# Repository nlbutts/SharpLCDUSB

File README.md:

# SharpLCDUSB
Small USB device for the Sharp Memory LCD

# Requirements

This was developed using Kicad 5.1.8.

Digikey Github library hash:
https://github.com/digikey/digikey-kicad-library
e10fdb74d46ad9f1668ed96b06f4c25e4f1bcf4c

My personal Kicad libraries:
https://github.com/nlbutts/KicadLib
dcbc8002b31520b4c2474bcd5f2975a0abc3e0ea

https://github.com/nlbutts/KicadFootprint
a663d1c8cb2ec06ade98de852019e83a467398e3

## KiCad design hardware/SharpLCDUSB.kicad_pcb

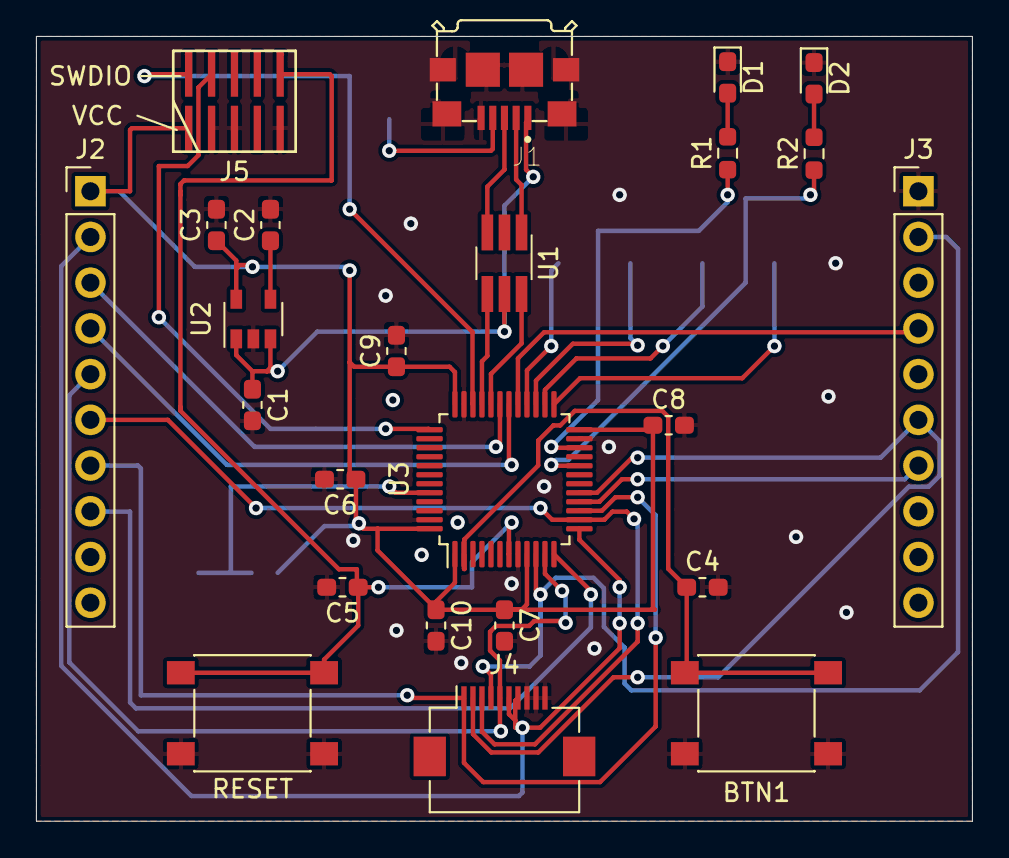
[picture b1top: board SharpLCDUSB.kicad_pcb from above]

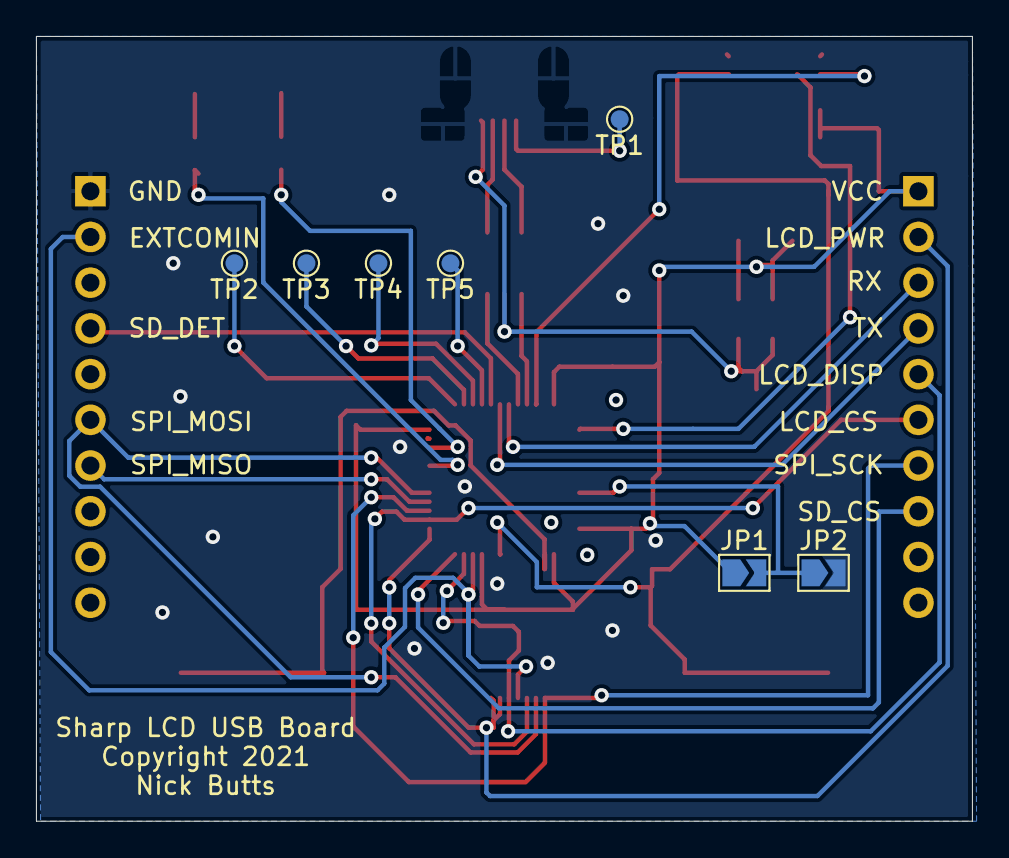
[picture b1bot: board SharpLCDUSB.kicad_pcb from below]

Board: 2 copper layers, 52.0 x 43.6 mm, 31 parts (7 on the bottom side), 33 nets.

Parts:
C1, C3: 10u; C_0603_1608Metric_Pad1.05x0.95mm_HandSolder
C2: 0.01u; C_0603_1608Metric_Pad1.05x0.95mm_HandSolder
C4, C5, C6, C7, C8: 0.1u; C_0603_1608Metric_Pad1.05x0.95mm_HandSolder
C9: 4.7u; C_0603_1608Metric_Pad1.05x0.95mm_HandSolder
C10: 1u; C_0603_1608Metric_Pad1.05x0.95mm_HandSolder
D1, D2: LED; LED_0603_1608Metric_Pad1.05x0.95mm_HandSolder
J1: A97800TR-ND; TE_1981568-1
J2, J3: Conn_01x10; PinHeader_1x10_P2.54mm_Vertical
J4: Conn_01x10; Hirose_FH12-10S-0.5SH_1x10-1MP_P0.50mm_Horizontal
J5: Conn_02x05_Odd_Even; FTSH-105-01-L-DV-K
JP1, JP2: SolderJumper_2_Bridged; SolderJumper-2_P1.3mm_Open_TrianglePad1.0x1.5mm
R1, R2: 330; R_0603_1608Metric_Pad0.98x0.95mm_HandSolder
SW1, SW2: SW_Push; SW_SPST_PTS645
TP1, TP2, TP3, TP4, TP5: TestPoint; TestPoint_Pad_D1.0mm
U1: USBLC6-2SC6; TSOT-23-6_HandSoldering
U2: TPS79333-EP; SOT-23-5
U3: STM32F303CCTx; LQFP-48_7x7mm_P0.5mm

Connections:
/BOOT0: JP1.2, JP2.1, U3.44
/DM: J1.2, U1.1
/DP: J1.3, U1.3
/EXTCOMIN: J3.2, J4.4, U3.10
/LCD_CS: J2.6, J4.3, U3.14
/LCD_DISP: J2.5, J4.5, U3.11
/LCD_PWR: J2.2, J4.6, J4.7, U3.13
/LED1: R1.1, U3.22
/LED2: R2.1, U3.20
/NRST: C5.1, J5.10, SW2.2, U3.7
/RX: J2.3, U3.31
/SD_CS: J2.8, U3.12
/SD_DET: J3.4, U3.29
/SPI_MISO: J3.7, U3.16
/SPI_MOSI: J3.6, J4.2, U3.17
/SPI_SCK: J2.7, J4.1, U3.15
/SWDCLK: J5.4, U3.37
/SWDIO: J5.2, U3.34
/TX: J2.4, U3.30
/USB_DM: U1.6, U3.32
/USB_DP: U1.4, U3.33
GND: C1.2, C2.2, C3.2, C4.2, C5.2, C6.2, C7.2, C8.2, C9.2, C10.2, D1.1, D2.1, J1.5, J3.1, J4.8, J4.9, J4.10, J5.3, J5.5, J5.9, JP2.2, SW1.1, SW2.1, U1.2, U2.2, U3.8, U3.23, U3.35, U3.47
unnamed: C2.1, U2.4
unnamed: C4.1, SW1.2, U3.2
unnamed: D1.2, R1.2
unnamed: D2.2, R2.2
unnamed: J1.4, TP1.1
unnamed: TP2.1, U3.25
unnamed: TP3.1, U3.26
unnamed: TP4.1, U3.27
unnamed: TP5.1, U3.28
VBUS: C1.1, J1.1, U1.5, U2.1, U2.3
VCC: C3.1, C6.1, C7.1, C8.1, C9.1, C10.1, J2.1, J5.1, JP1.1, U2.5, U3.1, U3.9, U3.24, U3.36, U3.48

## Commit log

2021-03-10 Initial checkin.
2021-03-10 Added rescue lib.
2021-03-11 Updated and routed.

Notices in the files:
hardware/SharpLCDUSB.kicad_pcb:
Copyright 2021
